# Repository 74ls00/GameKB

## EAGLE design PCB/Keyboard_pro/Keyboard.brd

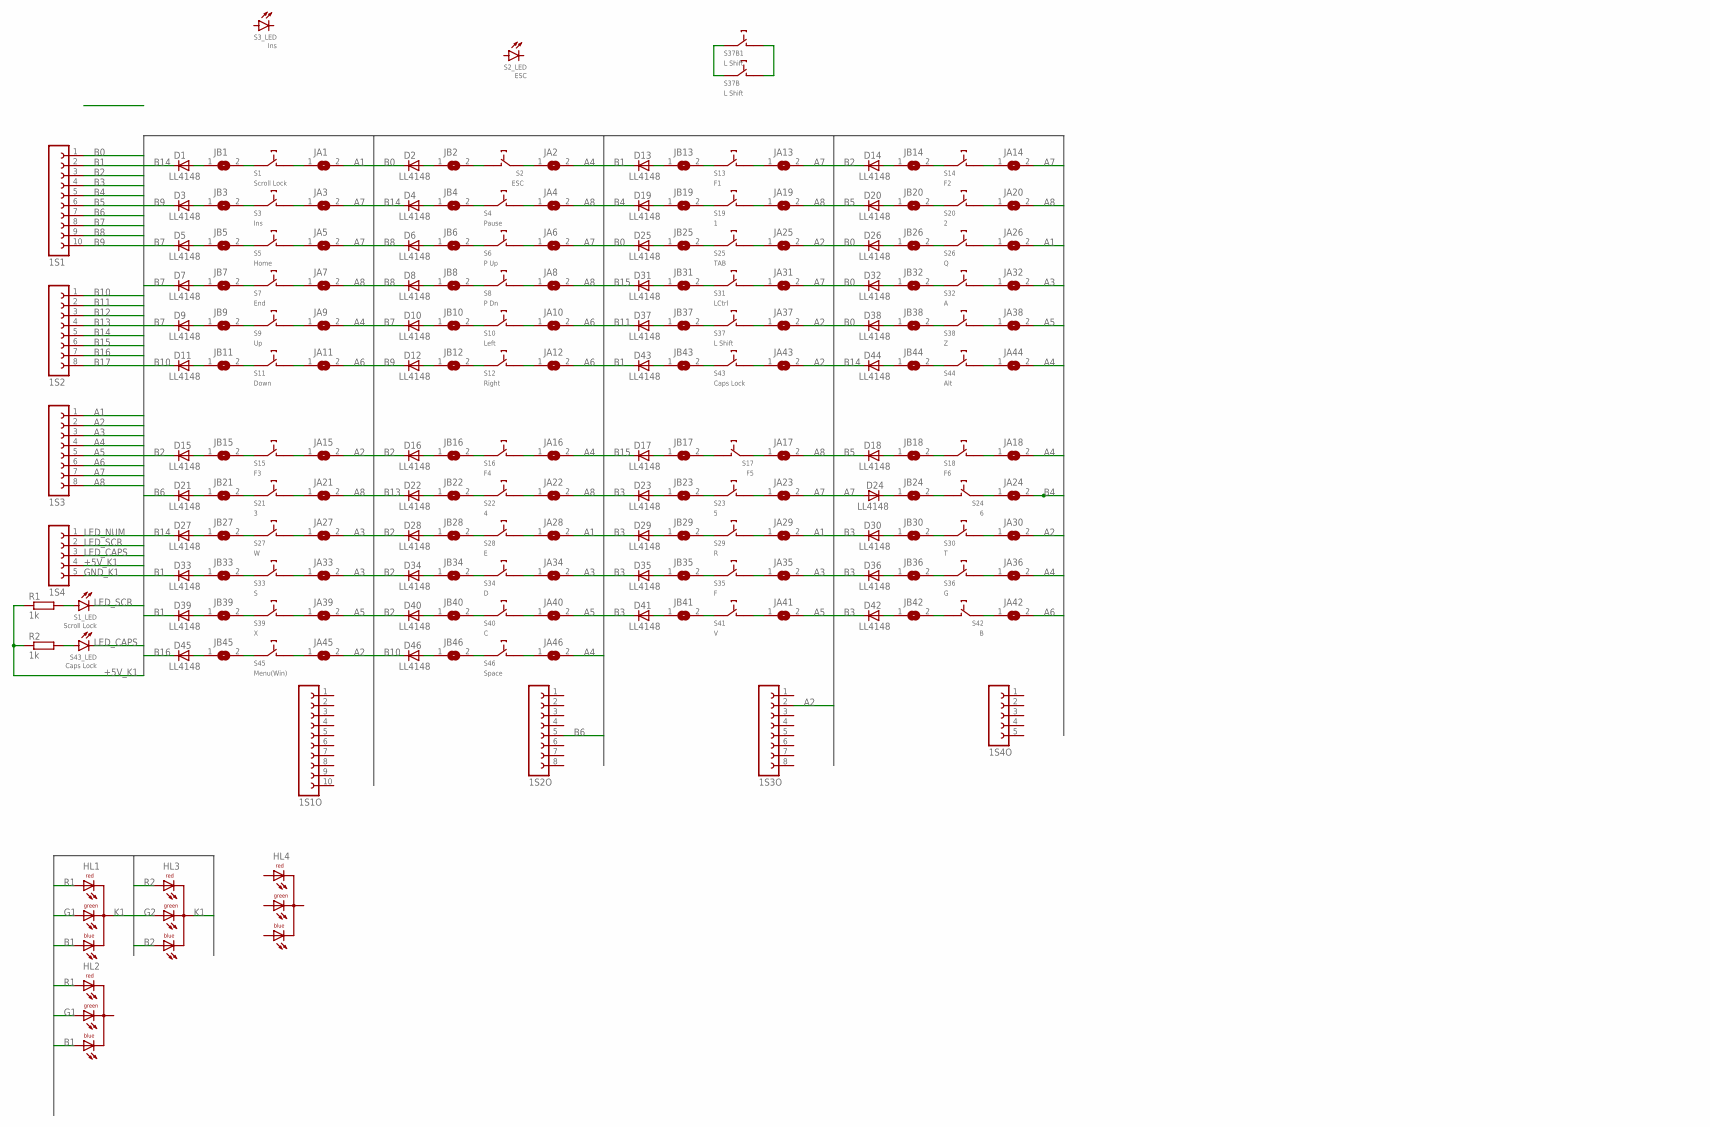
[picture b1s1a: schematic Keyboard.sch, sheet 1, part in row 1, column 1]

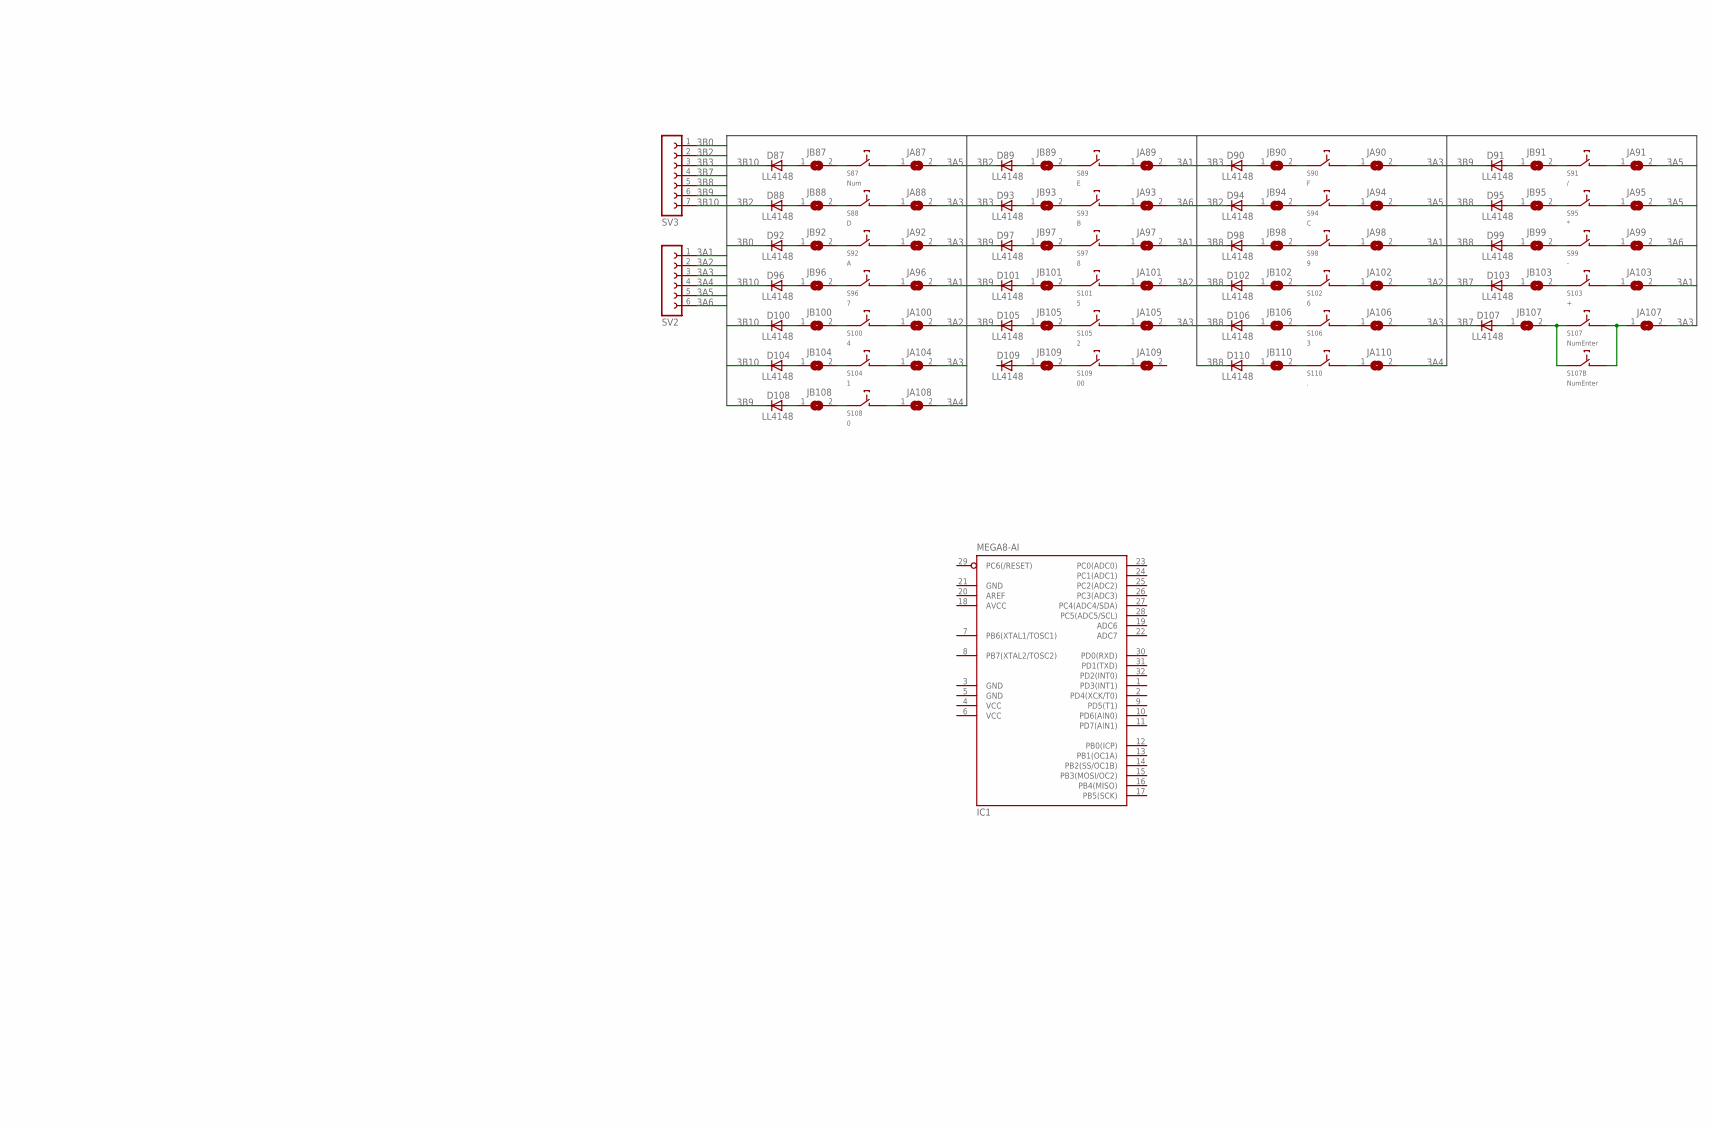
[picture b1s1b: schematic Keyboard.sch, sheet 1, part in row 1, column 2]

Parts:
1S1, 1S1O: FE10-1; FE10
1S2, 1S2O, 1S3, 1S3O: FE08-1; FE08
1S4, 1S4O: FE05-1
D1, D2, D3, D4, D5, D6, D7, D8, D9, D10, D11, D12, D13, D14, D15, D16, D17, D18, D19, D20, D21, D22, D23, D24, D25, D26, D27, D28, D29, D30, D31, D32, D33, D34, D35, D36, D37, D38, D39, D40, D41, D42, D43, D44, D45, D46, D87, D88, D89, D90, D91, D92, D93, D94, D95, D96, D97, D98, D99, D100, D101, D102, D103, D104, D105, D106, D107, D108, D109, D110: LL4148; SOD80C
HL1, HL2, HL3, HL4: RGB2X5
IC1: MEGA8-AI; TQFP32-08
JA1, JA2, JA3, JA4, JA5, JA6, JA7, JA8, JA9, JA10, JA11, JA12: SJ; SJ@1
JA13, JA14, JA15, JA16, JA17, JA18, JA19, JA20, JA21, JA22, JA23, JA24, JA25, JA26, JA27, JA28, JA29, JA30, JA31, JA32, JA33, JA34, JA35, JA36, JA37, JA38, JA39, JA40, JA41, JA42, JA43, JA44, JA45, JA46, JA87, JA88, JA89, JA90, JA91, JA92, JA93, JA94, JA95, JA96, JA97, JA98, JA99, JA100, JA101, JA102, JA103, JA104, JA105, JA106, JA107, JA108, JA109, JA110: SJ
JB1, JB3, JB18, JB19, JB20, JB21, JB22, JB23, JB24, JB25, JB26, JB27, JB28, JB29, JB30, JB31, JB32, JB33, JB34, JB35, JB36, JB37, JB38, JB39, JB40, JB41, JB42, JB43, JB44, JB45, JB46, JB87, JB88, JB89, JB90, JB91, JB92, JB93, JB94, JB95, JB96, JB97, JB98, JB99, JB100, JB101, JB102, JB103, JB104, JB105, JB106, JB107, JB108, JB109, JB110: SJ
JB2, JB4, JB5, JB6, JB7, JB8, JB9, JB10, JB11, JB12, JB13, JB14, JB15, JB16, JB17: SJ; SJ@1
R1, R2: 1k; R1206W
S1: Scroll Lock; CHERRY-MX-LED
S2: ESC; CHERRY-MX-LED
S3: Ins; CHERRY-MX-LED
S4: Pause; CHERRY-MX@1
S5: Home; CHERRY-MX
S6: P Up; CHERRY-MX
S7: End; CHERRY-MX
S8: P Dn; CHERRY-MX
S9: Up; CHERRY-MX
S10: Left; CHERRY-MX
S11: Down; CHERRY-MX
S12: Right; CHERRY-MX
S13: F1; CHERRY-MX
S14: F2; CHERRY-MX
S15: F3; CHERRY-MX
S16: F4; CHERRY-MX
S17: F5; CHERRY-MX
S18: F6; CHERRY-MX
S19: 1; CHERRY-MX
S20: 2; CHERRY-MX
S21: 3; CHERRY-MX
S22: 4; CHERRY-MX
S23: 5; CHERRY-MX
S24: 6; CHERRY-MX
S25: TAB; CHERRY-MX
S26: Q; CHERRY-MX
S27: W; CHERRY-MX@1
S28: E; CHERRY-MX
S29: R; CHERRY-MX
S30: T; CHERRY-MX
S31: LCtrl; CHERRY-MX
S32: A; CHERRY-MX
S33: S; CHERRY-MX
S34: D; CHERRY-MX
S35: F; CHERRY-MX
S36: G; CHERRY-MX
S37, S37B, S37B1: L Shift; CHERRY-MX
S38: Z; CHERRY-MX
S39: X; CHERRY-MX
S40: C; CHERRY-MX
S41: V; CHERRY-MX
S42: B; CHERRY-MX
S43: Caps Lock; CHERRY-MX-LED
S44: Alt; CHERRY-MX
S45: Menu(Win); CHERRY-MX
S46: Space; CHERRY-MX
S87: Num; CHERRY-MX-4P
S88: D; CHERRY-MX-4P
S89: E; CHERRY-MX-4P
S90: F; CHERRY-MX-4P
S91: /; CHERRY-MX-4P
S92: A; CHERRY-MX-4P
S93: B; CHERRY-MX-4P
S94: C; CHERRY-MX-4P
S95: *; CHERRY-MX-4P
S96: 7; CHERRY-MX-4P
S97: 8; CHERRY-MX-4P
S98: 9; CHERRY-MX-4P
S99: -; CHERRY-MX-4P
S100: 4; CHERRY-MX-4P
S101: 5; CHERRY-MX-4P
S102: 6; CHERRY-MX-4P
S103: +; CHERRY-MX-4P
S104: 1; CHERRY-MX-4P
S105: 2; CHERRY-MX-4P
S106: 3; CHERRY-MX-4P
S107: NumEnter; CHERRY-MX-4P
S107B: NumEnter; CHERRY-MX
S108: 0; CHERRY-MX-4P
S109: 00; CHERRY-MX-4P
S110: .; CHERRY-MX-4P
SV2: FE06-1; FE06
SV3: FE07-1; FE07

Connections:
3A1: JA89.2, JA96.2, JA97.2, JA98.2, JA103.2, SV2.1
3A2: JA100.2, JA101.2, JA102.2, SV2.2
3A3: JA88.2, JA90.2, JA92.2, JA104.2, JA105.2, JA106.2, JA107.2, SV2.3
3A4: JA108.2, JA110.2, SV2.4
3A5: JA87.2, JA91.2, JA94.2, JA95.2, SV2.5
3A6: JA93.2, JA99.2, SV2.6
3B0: D92.C, SV3.1
3B2: D88.C, D89.C, D94.C, SV3.2
3B3: D90.C, D93.C, SV3.3
3B7: D103.C, D107.C, SV3.4
3B8: D95.C, D98.C, D99.C, D102.C, D106.C, D110.C, SV3.5
3B9: D91.C, D97.C, D101.C, D105.C, D108.C, SV3.6
3B10: D87.C, D96.C, D100.C, D104.C, SV3.7
+5V_K1: 1S4.4, R1.1, R2.1
A1: 1S3.1, JA1.2, JA26.2, JA28.2, JA29.2
A2: 1S3.2, 1S3O.2, JA15.2, JA25.2, JA30.2, JA37.2, JA43.2, JA45.2
A3: 1S3.3, JA27.2, JA32.2, JA33.2, JA34.2, JA35.2
A4: 1S3.4, JA2.2, JA9.2, JA16.2, JA18.2, JA36.2, JA44.2, JA46.2
A5: 1S3.5, JA38.2, JA39.2, JA40.2, JA41.2
A6: 1S3.6, JA10.2, JA11.2, JA12.2, JA42.2
A7: 1S3.7, D24.A, JA3.2, JA5.2, JA6.2, JA13.2, JA14.2, JA23.2, JA31.2
A8: 1S3.8, JA4.2, JA7.2, JA8.2, JA17.2, JA19.2, JA20.2, JA21.2, JA22.2
AVCC: IC1.18 (AVCC)
B0: 1S1.1, D2.C, D25.C, D26.C, D32.C, D38.C
B1: 1S1.2, D13.C, D33.C, D39.C, D43.C, HL1.4 (AB), HL2.4 (AB)
B2: 1S1.3, D14.C, D15.C, D16.C, D28.C, D34.C, D40.C, HL3.4 (AB)
B3: 1S1.4, D23.C, D29.C, D30.C, D35.C, D36.C, D41.C, D42.C
B4: 1S1.5, D19.C, JA24.2
B5: 1S1.6, D18.C, D20.C
B6: 1S1.7, 1S2O.5, D21.C
B7: 1S1.8, D5.C, D7.C, D9.C, D10.C
B8: 1S1.9, D6.C, D8.C
B9: 1S1.10, D3.C, D12.C
B10: 1S2.1, D11.C, D46.C
B11: 1S2.2, D37.C
B12: 1S2.3
B13: 1S2.4, D22.C
B14: 1S2.5, D1.C, D4.C, D27.C, D44.C
B15: 1S2.6, D17.C, D31.C
B16: 1S2.7, D45.C
B17: 1S2.8
G1: HL1.3 (AG), HL2.3 (AG); also elsewhere on the board
G2: HL3.3 (AG); also elsewhere on the board
GND: IC1.3 (GND), IC1.5 (GND), IC1.21 (GND); also elsewhere on the board
GND_K1: 1S4.5
K1: HL1.2 (C), HL3.2 (C)
LED_CAPS: 1S4.3, S43.LED2
LED_NUM: 1S4.1
LED_SCR: 1S4.2, S1.LED2
unnamed: D15.A, JB15.1
unnamed: JB4.2, S4.SW1 (PIN-1)
unnamed: D1.A, JB1.1
unnamed: JA4.1, S4.SW2 (PIN-2)
unnamed: JB14.2, S14.SW1 (PIN-1)
unnamed: JB20.2, S20.SW1 (PIN-1)
unnamed: JB32.2, S32.SW1 (PIN-1)
unnamed: JB38.2, S38.SW1 (PIN-1)
unnamed: JB6.2, S6.SW1 (PIN-1)
unnamed: JA6.1, S6.SW2 (PIN-2)
unnamed: JA8.1, S8.SW2 (PIN-2)
unnamed: JB8.2, S8.SW1 (PIN-1)
unnamed: JB10.2, S10.SW1 (PIN-1)
unnamed: JB1.2, S1.SW1 (PIN-1)
unnamed: D2.A, JB2.1
unnamed: JB2.2, S2.SW2 (PIN-2)
unnamed: JA2.1, S2.SW1 (PIN-1)
unnamed: D16.A, JB16.1
unnamed: JB3.2, S3.SW1 (PIN-1)
unnamed: JB5.2, S5.SW1 (PIN-1)
unnamed: JB7.2, S7.SW1 (PIN-1)
unnamed: JB9.2, S9.SW1 (PIN-1)
unnamed: JB11.2, S11.SW1 (PIN-1)
unnamed: D3.A, JB3.1
unnamed: JB12.2, S12.SW1 (PIN-1)
unnamed: D5.A, JB5.1
unnamed: D7.A, JB7.1
unnamed: JA10.1, S10.SW2 (PIN-2)
unnamed: JA1.1, S1.SW2 (PIN-2)
unnamed: D9.A, JB9.1
unnamed: D11.A, JB11.1
unnamed: JA3.1, S3.SW2 (PIN-2)
unnamed: JA5.1, S5.SW2 (PIN-2)
unnamed: JA7.1, S7.SW2 (PIN-2)
unnamed: JA9.1, S9.SW2 (PIN-2)
unnamed: JA11.1, S11.SW2 (PIN-2)
unnamed: JA12.1, S12.SW2 (PIN-2)
unnamed: JA14.1, S14.SW2 (PIN-2)
unnamed: JB13.2, S13.SW1 (PIN-1)
unnamed: JA13.1, S13.SW2 (PIN-2)
unnamed: D14.A, JB14.1
unnamed: JB42.2, S42.SW2 (PIN-2)
unnamed: JA42.1, S42.SW1 (PIN-1)
unnamed: JB27.2, S27.SW1 (PIN-1)
unnamed: JA27.1, S27.SW2 (PIN-2)
unnamed: JB17.2, S17.SW2 (PIN-2)
unnamed: JA17.1, S17.SW1 (PIN-1)
unnamed: D24.C, JB24.1
unnamed: JB24.2, S24.SW2 (PIN-2)
unnamed: JA24.1, S24.SW1 (PIN-1)
unnamed: JA107.1, S107.SW2 (PIN-2), S107B.SW2 (PIN-2)
unnamed: D4.A, JB4.1
unnamed: D6.A, JB6.1
unnamed: D8.A, JB8.1
unnamed: D10.A, JB10.1
unnamed: D12.A, JB12.1
unnamed: D13.A, JB13.1
unnamed: JB19.2, S19.SW1 (PIN-1)
unnamed: JB25.2, S25.SW1 (PIN-1)
unnamed: D104.A, JB104.1
unnamed: JB31.2, S31.SW1 (PIN-1)
unnamed: JB37.2, S37.SW1 (PIN-1), S37B.SW1 (PIN-1), S37B1.SW1 (PIN-1)
unnamed: JB43.2, S43.SW1 (PIN-1)
unnamed: JB26.2, S26.SW1 (PIN-1)
unnamed: JB44.2, S44.SW1 (PIN-1)
unnamed: JB18.2, S18.SW1 (PIN-1)
unnamed: JB30.2, S30.SW1 (PIN-1)
unnamed: JB36.2, S36.SW1 (PIN-1)
unnamed: JB23.2, S23.SW1 (PIN-1)
unnamed: JB29.2, S29.SW1 (PIN-1)
unnamed: JB35.2, S35.SW1 (PIN-1)
unnamed: JB41.2, S41.SW1 (PIN-1)
unnamed: JB16.2, S16.SW1 (PIN-1)
unnamed: JB22.2, S22.SW1 (PIN-1)
unnamed: JB28.2, S28.SW1 (PIN-1)
unnamed: JB34.2, S34.SW1 (PIN-1)
unnamed: JB40.2, S40.SW1 (PIN-1)
unnamed: JB46.2, S46.SW1 (PIN-1)
unnamed: JB15.2, S15.SW1 (PIN-1)
unnamed: JB21.2, S21.SW1 (PIN-1)
unnamed: JB33.2, S33.SW1 (PIN-1)
unnamed: JB39.2, S39.SW1 (PIN-1)
unnamed: JB45.2, S45.SW1 (PIN-1)
unnamed: JA15.1, S15.SW2 (PIN-2)
unnamed: JA18.1, S18.SW2 (PIN-2)
unnamed: JA20.1, S20.SW2 (PIN-2)
unnamed: JA22.1, S22.SW2 (PIN-2)
unnamed: JA23.1, S23.SW2 (PIN-2)
unnamed: JA25.1, S25.SW2 (PIN-2)
unnamed: JA26.1, S26.SW2 (PIN-2)
unnamed: JA28.1, S28.SW2 (PIN-2)
unnamed: JA29.1, S29.SW2 (PIN-2)
unnamed: JA30.1, S30.SW2 (PIN-2)
unnamed: JA31.1, S31.SW2 (PIN-2)
unnamed: JA32.1, S32.SW2 (PIN-2)
unnamed: JA33.1, S33.SW2 (PIN-2)
unnamed: JA34.1, S34.SW2 (PIN-2)
unnamed: JA35.1, S35.SW2 (PIN-2)
unnamed: JA36.1, S36.SW2 (PIN-2)
unnamed: JA37.1, S37.SW2 (PIN-2), S37B.SW2 (PIN-2), S37B1.SW2 (PIN-2)
unnamed: JA38.1, S38.SW2 (PIN-2)
unnamed: JA39.1, S39.SW2 (PIN-2)
unnamed: JA40.1, S40.SW2 (PIN-2)
unnamed: JA41.1, S41.SW2 (PIN-2)
unnamed: JA43.1, S43.SW2 (PIN-2)
unnamed: JA45.1, S45.SW2 (PIN-2)
unnamed: JA46.1, S46.SW2 (PIN-2)
unnamed: JA19.1, S19.SW2 (PIN-2)
unnamed: JA44.1, S44.SW2 (PIN-2)
unnamed: JA21.1, S21.SW2 (PIN-2)
unnamed: JA16.1, S16.SW2 (PIN-2)
unnamed: D17.A, JB17.1
unnamed: D18.A, JB18.1
unnamed: D19.A, JB19.1
unnamed: D20.A, JB20.1
unnamed: D21.A, JB21.1
unnamed: D22.A, JB22.1
unnamed: D23.A, JB23.1
unnamed: D25.A, JB25.1
unnamed: D26.A, JB26.1
unnamed: D27.A, JB27.1
unnamed: D28.A, JB28.1
unnamed: D29.A, JB29.1
unnamed: D30.A, JB30.1
unnamed: D31.A, JB31.1
unnamed: D32.A, JB32.1
unnamed: D33.A, JB33.1
unnamed: D34.A, JB34.1
unnamed: D35.A, JB35.1
unnamed: D36.A, JB36.1
unnamed: D37.A, JB37.1
unnamed: D38.A, JB38.1
unnamed: D39.A, JB39.1
unnamed: D40.A, JB40.1
unnamed: D41.A, JB41.1
unnamed: D42.A, JB42.1
unnamed: D43.A, JB43.1
unnamed: D44.A, JB44.1
unnamed: D45.A, JB45.1
unnamed: D46.A, JB46.1
unnamed: R1.2, S1.LED1
unnamed: R2.2, S43.LED1
unnamed: D87.A, JB87.1
unnamed: D88.A, JB88.1
unnamed: JB87.2, S87.SW1 (PIN-1)
unnamed: JB88.2, S88.SW1 (PIN-1)
unnamed: JA87.1, S87.SW2 (PIN-2)
unnamed: JA88.1, S88.SW2 (PIN-2)
unnamed: D89.A, JB89.1
unnamed: JB89.2, S89.SW1 (PIN-1)
unnamed: JA89.1, S89.SW2 (PIN-2)
unnamed: D90.A, JB90.1
unnamed: JB90.2, S90.SW1 (PIN-1)
unnamed: JA90.1, S90.SW2 (PIN-2)
unnamed: D91.A, JB91.1
unnamed: JB91.2, S91.SW1 (PIN-1)
unnamed: JA91.1, S91.SW2 (PIN-2)
unnamed: JB92.2, S92.SW1 (PIN-1)
unnamed: D92.A, JB92.1
unnamed: JA92.1, S92.SW2 (PIN-2)
unnamed: JA93.1, S93.SW2 (PIN-2)
unnamed: JB93.2, S93.SW1 (PIN-1)
unnamed: D93.A, JB93.1
unnamed: D94.A, JB94.1
unnamed: JB94.2, S94.SW1 (PIN-1)
unnamed: JA94.1, S94.SW2 (PIN-2)
unnamed: D95.A, JB95.1
unnamed: JB95.2, S95.SW1 (PIN-1)
unnamed: JA95.1, S95.SW2 (PIN-2)
unnamed: D96.A, JB96.1
unnamed: JB96.2, S96.SW1 (PIN-1)
unnamed: JA96.1, S96.SW2 (PIN-2)
unnamed: JB97.2, S97.SW1 (PIN-1)
unnamed: JA97.1, S97.SW2 (PIN-2)
unnamed: D97.A, JB97.1
unnamed: D98.A, JB98.1
unnamed: JB98.2, S98.SW1 (PIN-1)
unnamed: JA98.1, S98.SW2 (PIN-2)
unnamed: D99.A, JB99.1
unnamed: JB99.2, S99.SW1 (PIN-1)
unnamed: JA99.1, S99.SW2 (PIN-2)
unnamed: D100.A, JB100.1
unnamed: JB100.2, S100.SW1 (PIN-1)
unnamed: JA100.1, S100.SW2 (PIN-2)
unnamed: JB101.2, S101.SW1 (PIN-1)
unnamed: D101.A, JB101.1
unnamed: JA101.1, S101.SW2 (PIN-2)
unnamed: D102.A, JB102.1
unnamed: JB102.2, S102.SW1 (PIN-1)
unnamed: JA102.1, S102.SW2 (PIN-2)
unnamed: D103.A, JB103.1
unnamed: JB103.2, S103.SW1 (PIN-1)
unnamed: JA103.1, S103.SW2 (PIN-2)
unnamed: JB107.2, S107.SW1 (PIN-1), S107B.SW1 (PIN-1)
unnamed: JB104.2, S104.SW1 (PIN-1)
unnamed: JA104.1, S104.SW2 (PIN-2)
unnamed: JB105.2, S105.SW1 (PIN-1)
unnamed: D105.A, JB105.1
unnamed: JA105.1, S105.SW2 (PIN-2)
unnamed: D106.A, JB106.1
unnamed: JB106.2, S106.SW1 (PIN-1)
unnamed: JA106.1, S106.SW2 (PIN-2)
unnamed: D107.A, JB107.1
unnamed: JB108.2, S108.SW1 (PIN-1)
unnamed: JA108.1, S108.SW2 (PIN-2)
unnamed: D108.A, JB108.1
unnamed: JB109.2, S109.SW1 (PIN-1)
unnamed: D109.A, JB109.1
unnamed: JA109.1, S109.SW2 (PIN-2)
unnamed: D110.A, JB110.1
unnamed: JB110.2, S110.SW1 (PIN-1)
unnamed: JA110.1, S110.SW2 (PIN-2)
R1: HL1.1 (AR), HL2.1 (AR)
R2: HL3.1 (AR)
VCC: IC1.4 (VCC), IC1.6 (VCC)

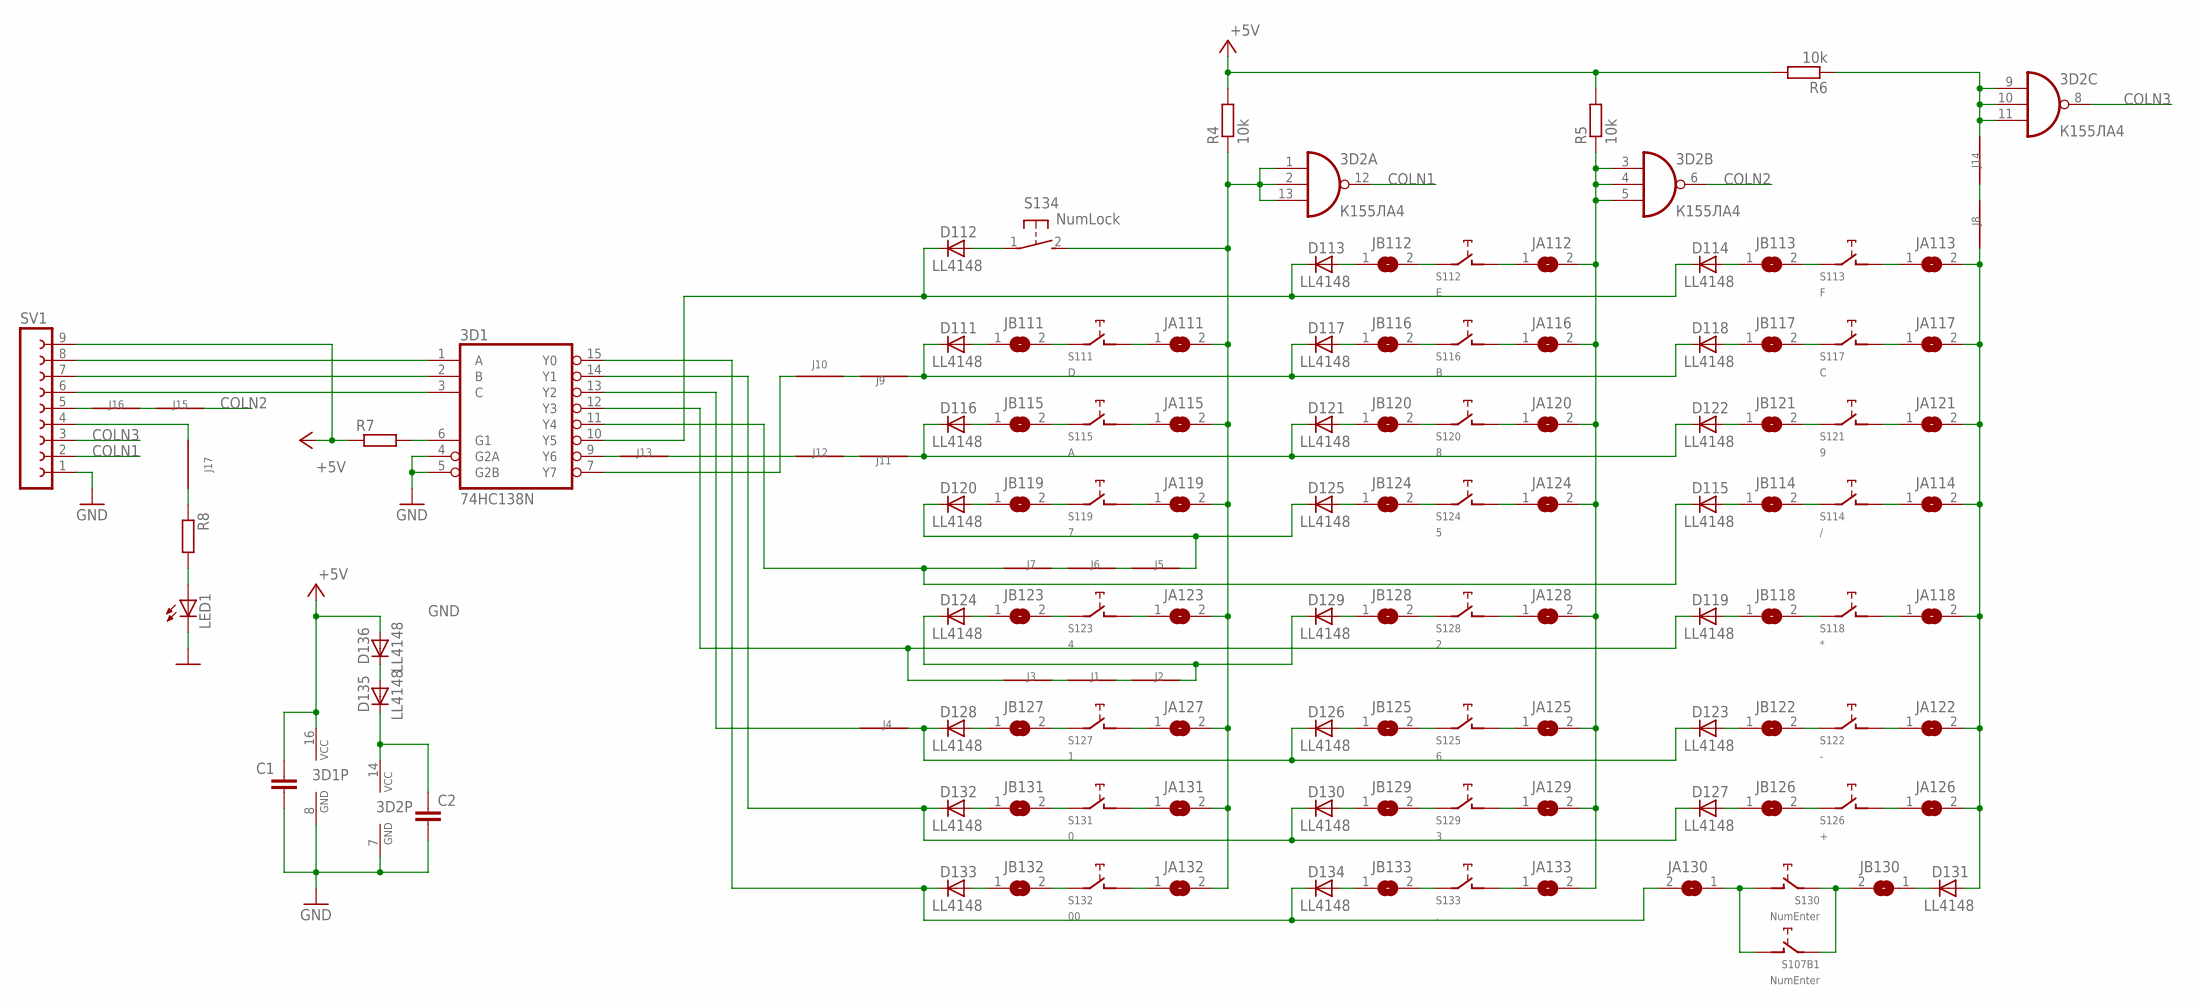
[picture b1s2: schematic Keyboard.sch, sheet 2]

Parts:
3D1: 74HC138N; DIL16
3D2: К155ЛА4; DIL14
C1, C2: C-EUC1206; C1206
D111, D112, D113, D114, D115, D116, D117, D118, D119, D120, D121, D122, D123, D124, D125, D126, D127, D128, D129, D130, D131, D132, D133, D134, D135, D136: LL4148; SOD80C
J1, J2, J3, J4, J5, J6, J7, J8, J9, J10, J11, J12, J13, J14, J15, J16, J17: J; R1206W
JA111, JA112, JA113, JA114, JA115, JA116, JA117, JA118, JA119, JA120, JA121, JA122, JA123, JA124, JA125, JA126, JA127, JA128, JA129, JA130, JA131, JA132, JA133: SJ
JB111, JB112, JB113, JB114, JB115, JB116, JB117, JB118, JB119, JB120, JB121, JB122, JB123, JB124, JB125, JB126, JB127, JB128, JB129, JB130, JB131, JB132, JB133: SJ
LED1: LED5MM
R4, R5, R6: 10k; R1206W
R7, R8: R-EU_R1206W; R1206W
S107B1, S130: NumEnter; CHERRY-MX-4P
S111: D; CHERRY-MX-4P
S112: E; CHERRY-MX-4P
S113: F; CHERRY-MX-4P
S114: /; CHERRY-MX-4P
S115: A; CHERRY-MX-4P
S116: B; CHERRY-MX-4P
S117: C; CHERRY-MX-4P
S118: *; CHERRY-MX-4P
S119: 7; CHERRY-MX-4P
S120: 8; CHERRY-MX-4P
S121: 9; CHERRY-MX-4P
S122: -; CHERRY-MX-4P
S123: 4; CHERRY-MX-4P
S124: 5; CHERRY-MX-4P
S125: 6; CHERRY-MX-4P
S126: +; CHERRY-MX-4P
S127: 1; CHERRY-MX-4P
S128: 2; CHERRY-MX-4P
S129: 3; CHERRY-MX-4P
S131: 0; CHERRY-MX-4P
S132: 00; CHERRY-MX-4P
S133: .; CHERRY-MX-4P
S134: NumLock; B3F-31XX
SV1: FE09-1; FE09

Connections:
+5V: 3D1.16 (VCC), C1.1, D136.A, R4.2, R5.2, R6.2, R7.1, SV1.9; also elsewhere on the board
COLN1: 3D2.12 (O), SV1.2
COLN2: 3D2.6 (O), J15.1
COLN3: 3D2.8 (O), SV1.3
GND: 3D1.4 (G2A), 3D1.5 (G2B), 3D1.8 (GND), 3D2.7 (GND), C1.2, C2.2, LED1.K (C), SV1.1; also elsewhere on the board
unnamed: D112.A, S134.1
unnamed: JA111.1, S111.SW2 (PIN-2)
unnamed: D113.A, JB112.1
unnamed: JB112.2, S112.SW1 (PIN-1)
unnamed: JA112.1, S112.SW2 (PIN-2)
unnamed: D111.A, JB111.1
unnamed: JB111.2, S111.SW1 (PIN-1)
unnamed: D114.A, JB113.1
unnamed: JB113.2, S113.SW1 (PIN-1)
unnamed: JA113.1, S113.SW2 (PIN-2)
unnamed: D115.A, JB114.1
unnamed: JB114.2, S114.SW1 (PIN-1)
unnamed: JA114.1, S114.SW2 (PIN-2)
unnamed: JB115.2, S115.SW1 (PIN-1)
unnamed: D116.A, JB115.1
unnamed: JA115.1, S115.SW2 (PIN-2)
unnamed: JA116.1, S116.SW2 (PIN-2)
unnamed: JB116.2, S116.SW1 (PIN-1)
unnamed: D117.A, JB116.1
unnamed: D118.A, JB117.1
unnamed: JB117.2, S117.SW1 (PIN-1)
unnamed: JA117.1, S117.SW2 (PIN-2)
unnamed: D119.A, JB118.1
unnamed: JB118.2, S118.SW1 (PIN-1)
unnamed: JA118.1, S118.SW2 (PIN-2)
unnamed: D120.A, JB119.1
unnamed: JB119.2, S119.SW1 (PIN-1)
unnamed: JA119.1, S119.SW2 (PIN-2)
unnamed: JB120.2, S120.SW1 (PIN-1)
unnamed: JA120.1, S120.SW2 (PIN-2)
unnamed: D121.A, JB120.1
unnamed: D122.A, JB121.1
unnamed: JB121.2, S121.SW1 (PIN-1)
unnamed: JA121.1, S121.SW2 (PIN-2)
unnamed: D123.A, JB122.1
unnamed: JB122.2, S122.SW1 (PIN-1)
unnamed: JA122.1, S122.SW2 (PIN-2)
unnamed: D124.A, JB123.1
unnamed: JB123.2, S123.SW1 (PIN-1)
unnamed: JA123.1, S123.SW2 (PIN-2)
unnamed: JB124.2, S124.SW1 (PIN-1)
unnamed: D125.A, JB124.1
unnamed: JA124.1, S124.SW2 (PIN-2)
unnamed: D126.A, JB125.1
unnamed: JB125.2, S125.SW1 (PIN-1)
unnamed: JA125.1, S125.SW2 (PIN-2)
unnamed: D127.A, JB126.1
unnamed: JB126.2, S126.SW1 (PIN-1)
unnamed: JA126.1, S126.SW2 (PIN-2)
unnamed: JB130.2, S107B1.SW1 (PIN-1), S130.SW1 (PIN-1)
unnamed: JA130.1, S107B1.SW2 (PIN-2), S130.SW2 (PIN-2)
unnamed: D128.A, JB127.1
unnamed: JB127.2, S127.SW1 (PIN-1)
unnamed: JA127.1, S127.SW2 (PIN-2)
unnamed: JB128.2, S128.SW1 (PIN-1)
unnamed: D129.A, JB128.1
unnamed: JA128.1, S128.SW2 (PIN-2)
unnamed: D130.A, JB129.1
unnamed: JB129.2, S129.SW1 (PIN-1)
unnamed: JA129.1, S129.SW2 (PIN-2)
unnamed: JB131.2, S131.SW1 (PIN-1)
unnamed: JA131.1, S131.SW2 (PIN-2)
unnamed: D132.A, JB131.1
unnamed: JB132.2, S132.SW1 (PIN-1)
unnamed: D133.A, JB132.1
unnamed: JA132.1, S132.SW2 (PIN-2)
unnamed: D134.A, JB133.1
unnamed: JB133.2, S133.SW1 (PIN-1)
unnamed: JA133.1, S133.SW2 (PIN-2)
unnamed: 3D2.3 (I0), 3D2.4 (I1), 3D2.5 (I2), JA112.2, JA116.2, JA120.2, JA124.2, JA125.2, JA128.2, JA129.2, JA133.2, R5.1
unnamed: D111.C, D117.C, D118.C, J9.2
unnamed: D123.C, D126.C, D128.C, J4.1
unnamed: 3D2.1 (I0), 3D2.2 (I1), 3D2.13 (I2), JA111.2, JA115.2, JA119.2, JA123.2, JA127.2, JA131.2, JA132.2, R4.1, S134.2 (S)
unnamed: 3D1.10 (Y5), D112.C, D113.C, D114.C
unnamed: 3D1.11 (Y4), D115.C, J7.2
unnamed: 3D1.12 (Y3), D119.C, J3.2
unnamed: 3D1.14 (Y1), D127.C, D130.C, D132.C
unnamed: D116.C, D121.C, D122.C, J11.2
unnamed: D131.A, J8.2, JA113.2, JA114.2, JA117.2, JA118.2, JA121.2, JA122.2, JA126.2
unnamed: D131.C, JB130.1
unnamed: D124.C, D129.C, J2.1
unnamed: J1.1, J2.2
unnamed: J1.2, J3.1
unnamed: 3D1.13 (Y2), J4.2
unnamed: D120.C, D125.C, J5.1
unnamed: J6.2, J7.1
unnamed: J5.2, J6.1
unnamed: 3D2.9 (I0), 3D2.10 (I1), 3D2.11 (I2), J14.1, R6.1
unnamed: 3D1.7 (Y7), J10.1
unnamed: J9.1, J10.2
unnamed: J11.1, J12.1
unnamed: J12.2, J13.1
unnamed: 3D1.9 (Y6), J13.2
unnamed: 3D1.6 (G1), R7.2
unnamed: 3D1.1 (A), SV1.8
unnamed: 3D1.2 (B), SV1.7
unnamed: 3D1.3 (C), SV1.6
unnamed: LED1.A, R8.2
unnamed: J8.1, J14.2
unnamed: J15.2, J16.1
unnamed: J16.2, SV1.5
unnamed: J17.2, SV1.4
unnamed: J17.1, R8.1
unnamed: D135.A, D136.C
unnamed: 3D2.14 (VCC), C2.1, D135.C
SCK: 3D1.15 (Y0), D133.C, D134.C, JA130.2
